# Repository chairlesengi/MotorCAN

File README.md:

# MotorCAN
CANBus based FOC motor driver board designed for drone gimbal motors for node-based control, designed in KiCad.

Features:
  - STM32G431 processor core for SimpleFOC software and CAN communication
  - 3.3V CAN communication for easy logic level support
  - Runs on 20-26V DC
  - Integrated magnetic absolute encoder (MT6816CT)
  - Handles up to ~3A of motor current

This driver is designed to be a fully integrated solution that mounts to the back of a gimbal motor with a diametrically magnetized magnet. For that reason, it includes an absoulute magnetic encoder and leverages the current sensing capabilities of the DRV8316C driver to maintain a continous measurement of the position of the rotor of the motor and its magnetic field. Then, the STM32 running SimpleFOC calculates the exact currents on each phase needed to create a magnetic torque on the motor that is 90 degrees from the magnetic field and therefore gives the greatest overall control of the motor. This chip also has a 3.3V CAN chip so it can link up to a simple 4 wire network of muliple of these boards for applications like camera gimbals.

Credits:
SimpleFOC: https://github.com/simplefoc
KiCad: https://www.kicad.org

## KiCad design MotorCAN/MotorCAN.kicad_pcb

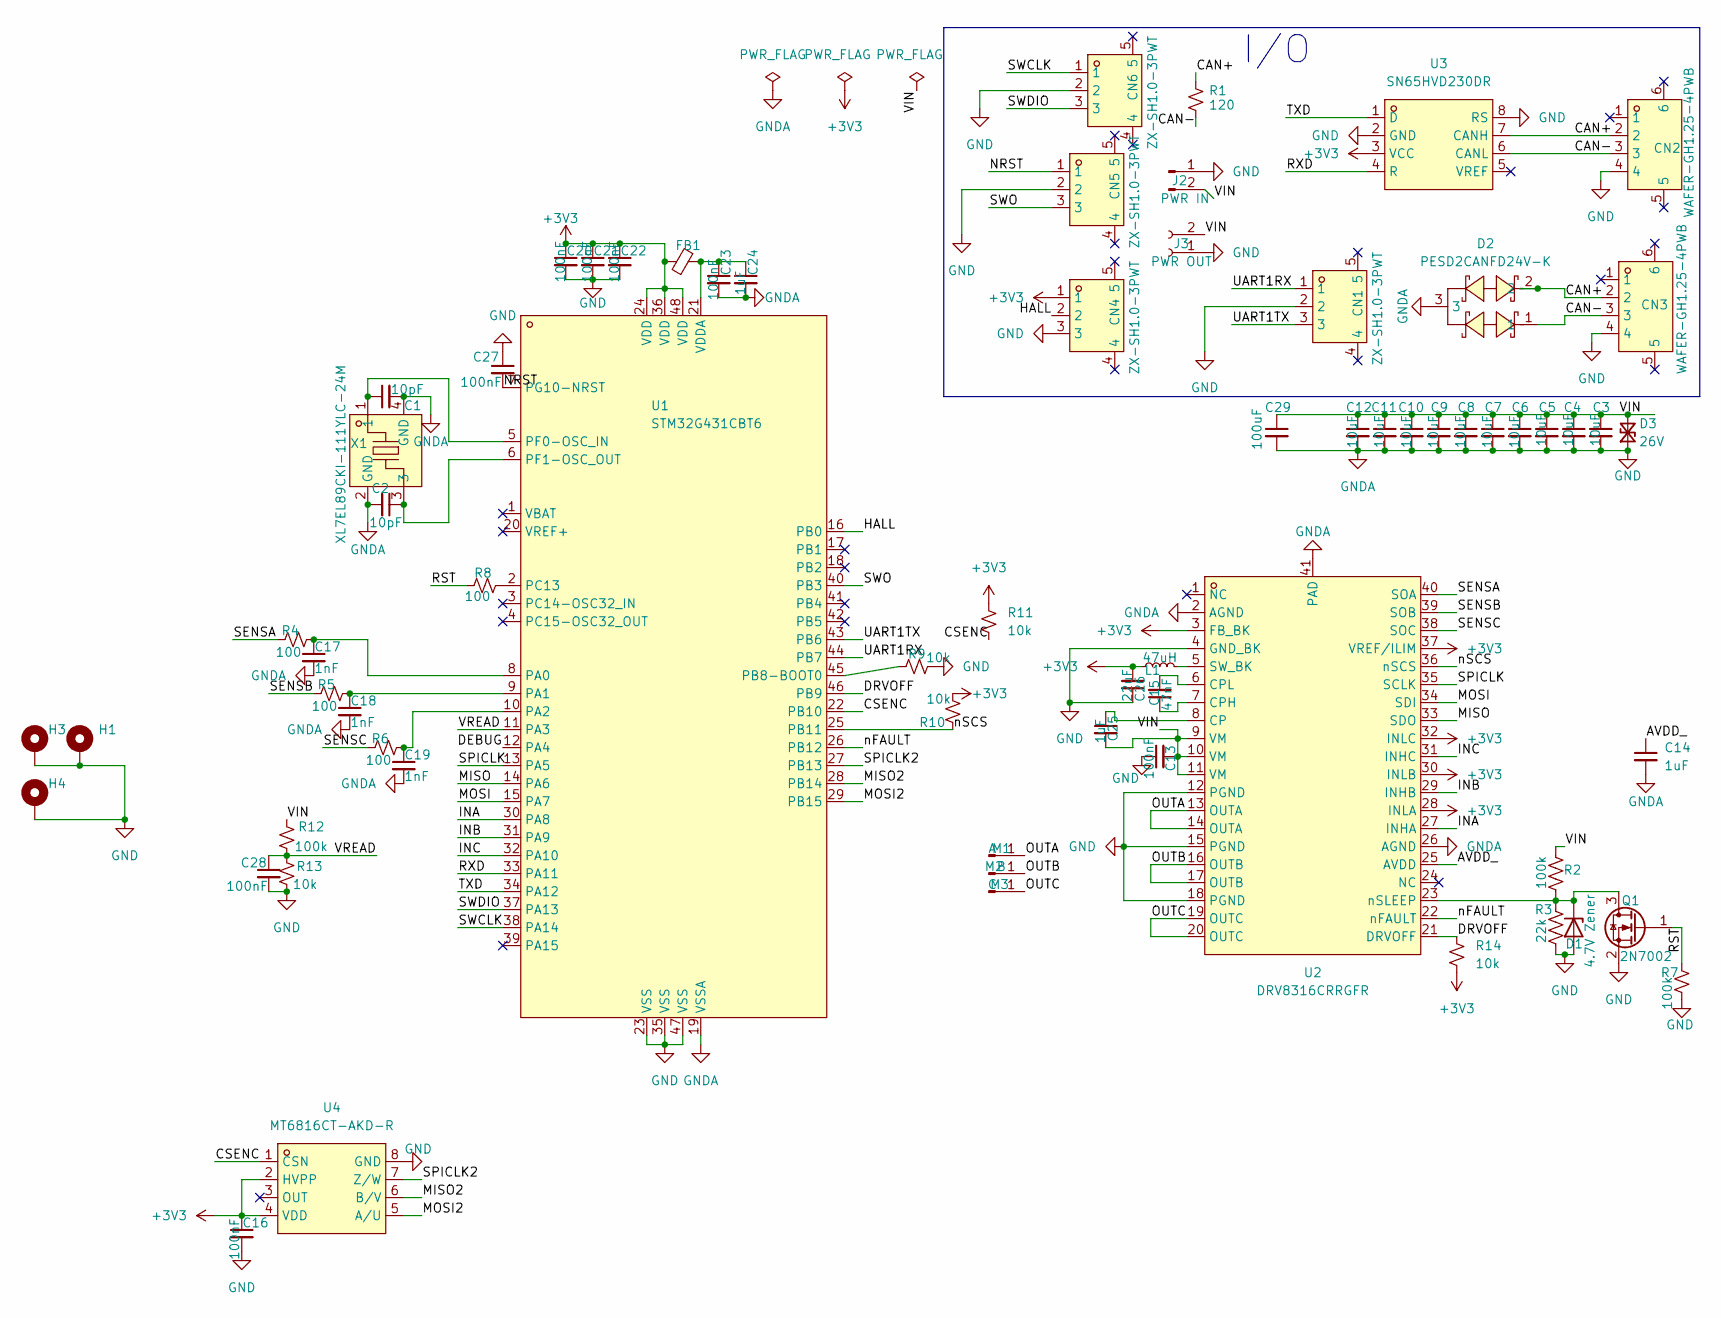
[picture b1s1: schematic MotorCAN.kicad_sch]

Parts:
C1, C2: 10pF; C_0402_1005Metric
C3, C4, C5, C6, C7, C8, C9, C10, C11, C12: 10uF; C_1206_3216Metric
C13, C16, C20, C21, C22, C23, C27, C28: 100nF; C_0402_1005Metric
C14, C24, C25: 1uF; C_0603_1608Metric
C15: 47nF; C_0603_1608Metric
C17, C18, C19: 1nF; C_0603_1608Metric
C26: 22uF; C_1206_3216Metric
C29: 100uF; CP_Elec_6.3x7.7
CN1, CN4, CN5, CN6: ZX-SH1.0-3PWT; CONN-SMD_3P-P1.00_MEGASTAR_ZX-SH1.0-3PWT; MPN ZX-SH1.0-3PWT; LCSC Part C7430445
CN2, CN3: WAFER-GH1.25-4PWB; CONN-SMD_4P-P1.25_XUNPU_WAFER-GH1.25-4PWB; MPN WAFER-GH1.25-4PWB; LCSC Part C3029379
D1: 4.7V Zener; D_SOD-123
D2: PESD2CANFD24V-K; SOT-23-3_L2.9-W1.3-P1.90-LS2.4-BR; MPN PESD2CANFD24V-K; LCSC Part C5278878
D3: 26V; D_SMB
FB1: 600@100MHz; R_0603_1608Metric
H1, H3, H4: MountingHole_Pad; MountingHole_2.2mm_M2_ISO14580_Pad_TopBottom
J2: PWR IN; AMASS_XT30PW-M_1x02_P2.50mm_Horizontal
J3: PWR OUT; AMASS_XT30PW-F_1x02_P2.50mm_Horizontal
L1: 47uH; IND-SMD_L4.0-W4.0
M1: A; SolderWirePad_1x01_SMD_2x4mm
M2: B; SolderWirePad_1x01_SMD_2x4mm
M3: C; SolderWirePad_1x01_SMD_2x4mm
Q1: 2N7002; SOT-23
R1: 120; R_0603_1608Metric
R2, R7, R12: 100k; R_0603_1608Metric
R3: 22k; R_0603_1608Metric
R4, R5, R6, R8: 100; R_0603_1608Metric
R9, R10, R11, R13, R14: 10k; R_0603_1608Metric
U1: STM32G431CBT6; LQFP-48_L7.0-W7.0-P0.50-LS9.0-BL; MPN STM32G431CBT6; LCSC Part C529355
U2: DRV8316CRRGFR; VQFN-40_L7.0-W5.0-P0.50-BL-EP5.7; MPN DRV8316CRRGFR; LCSC Part C5447274
U3: SN65HVD230DR; SOIC-8_L4.9-W3.9-P1.27-LS6.0-BL; MPN SN65HVD230DR; LCSC Part C12084
U4: MT6816CT-AKD-R; SOP-8_L4.9-W3.9-P1.27-LS6.0-BL-1; MPN MT6816CT-AKD-R; LCSC Part C2987620
X1: XL7EL89CKI-111YLC-24M; CRYSTAL-SMD_4P-L2.0-W1.6-BL-A; MPN XL7EL89CKI-111YLC-24M; LCSC Part C2965580

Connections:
+3V3: C16.1, C20.1, C21.1, C22.1, C26.2, CN4.1, FB1.1, L1.1, R10.1, R11.1, R14.2, U1.24 (VDD), U1.36 (VDD), U1.48 (VDD), U2.3 (FB_BK), U2.28 (INLA), U2.30 (INLB), U2.32 (INLC), U2.37 (VREF/ILIM), U3.3 (VCC), U4.2 (HVPP), U4.4 (VDD)
/AVDD_: C14.1, U2.25 (AVDD)
/CAN+: CN2.2, CN3.2, D2.2, R1.1, U3.7 (CANH)
/CAN-: CN2.3, CN3.3, D2.1, R1.2, U3.6 (CANL)
/CSENC: R11.2, U1.22 (PB10), U4.1 (CSN)
/DEBUG: U1.12 (PA4)
/DRVOFF: R14.1, U1.46 (PB9), U2.21 (DRVOFF)
/HALL: CN4.2, U1.16 (PB0)
/INA: U1.30 (PA8), U2.27 (INHA)
/INB: U1.31 (PA9), U2.29 (INHB)
/INC: U1.32 (PA10), U2.31 (INHC)
/MISO: U1.14 (PA6), U2.33 (SDO)
/MISO2: U1.28 (PB14), U4.6 (B/V)
/MOSI: U1.15 (PA7), U2.34 (SDI)
/MOSI2: U1.29 (PB15), U4.5 (A/U)
/NRST: C27.2, CN5.1, U1.7 (PG10-NRST)
/OUTA: M1.1 (Pin_1_1), U2.13 (OUTA), U2.14 (OUTA)
/OUTB: M2.1 (Pin_1_1), U2.16 (OUTB), U2.17 (OUTB)
/OUTC: M3.1 (Pin_1_1), U2.19 (OUTC), U2.20 (OUTC)
/RST: Q1.1 (G), R7.1, R8.1
/RXD: U1.33 (PA11), U3.4 (R)
/SENSA: R4.1, U2.40 (SOA)
/SENSB: R5.1, U2.39 (SOB)
/SENSC: R6.1, U2.38 (SOC)
/SPICLK: U1.13 (PA5), U2.35 (SCLK)
/SPICLK2: U1.27 (PB13), U4.7 (Z/W)
/SWCLK: CN6.1, U1.38 (PA14)
/SWDIO: CN6.3, U1.37 (PA13)
/SWO: CN5.3, U1.40 (PB3)
/TXD: U1.34 (PA12), U3.1 (D)
/UART1RX: CN1.1, U1.44 (PB7)
/UART1TX: CN1.3, U1.43 (PB6)
/VIN: C3.1, C4.1, C5.1, C6.1, C7.1, C8.1, C9.1, C10.1, C11.1, C12.1, C13.2, C25.2, C29.1, D3.2 (A2), J2.2, J3.2, R2.1, R12.1, U2.9 (VM), U2.10 (VM), U2.11 (VM)
/VREAD: C28.1, R12.2, R13.1, U1.11 (PA3)
/nFAULT: U1.26 (PB12), U2.22 (nFAULT)
/nSCS: R10.2, U1.25 (PB11), U2.36 (nSCS)
GND: C1.2, C2.2, C3.2, C4.2, C5.2, C6.2, C7.2, C8.2, C9.2, C10.2, C11.2, C12.2, C13.1, C14.2, C16.2, C17.2, C18.2, C19.2, C20.2, C21.2, C22.2, C23.2, C24.2, C26.1, C27.1, C28.2, C29.2, CN1.2, CN2.4, CN3.4, CN4.3, CN5.2, CN6.2, D1.2 (A), D2.3, D3.1 (A1), H1.1 (1_1), H3.1 (1_1), H4.1 (1_1), J2.1, J3.1, Q1.2 (S), R3.2, R7.2, R9.2, R13.2, U1.19 (VSSA), U1.23 (VSS), U1.35 (VSS), U1.47 (VSS), U2.2 (AGND), U2.4 (GND_BK), U2.12 (PGND), U2.15 (PGND), U2.18 (PGND), U2.26 (AGND), U2.41 (PAD), U3.2 (GND), U3.8 (RS), U4.8 (GND), X1.2 (GND), X1.4 (GND)
unnamed: D1.1 (K), Q1.3 (D), R2.2, R3.1, U2.23 (nSLEEP)
unnamed: C17.1, R4.2, U1.8 (PA0)
unnamed: C18.1, R5.2, U1.9 (PA1)
unnamed: C19.1, R6.2, U1.10 (PA2)
unnamed: R9.1, U1.45 (PB8-BOOT0)
unnamed: R8.2, U1.2 (PC13)
unnamed: C1.1, U1.5 (PF0-OSC_IN), X1.1
unnamed: C2.1, U1.6 (PF1-OSC_OUT), X1.3
unnamed: C23.1, C24.1, FB1.2, U1.21 (VDDA)
unnamed: C25.1, U2.8 (CP)
unnamed: C15.1, U2.7 (CPH)
unnamed: C15.2, U2.6 (CPL)
unnamed: L1.2, U2.5 (SW_BK)

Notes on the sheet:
I/O

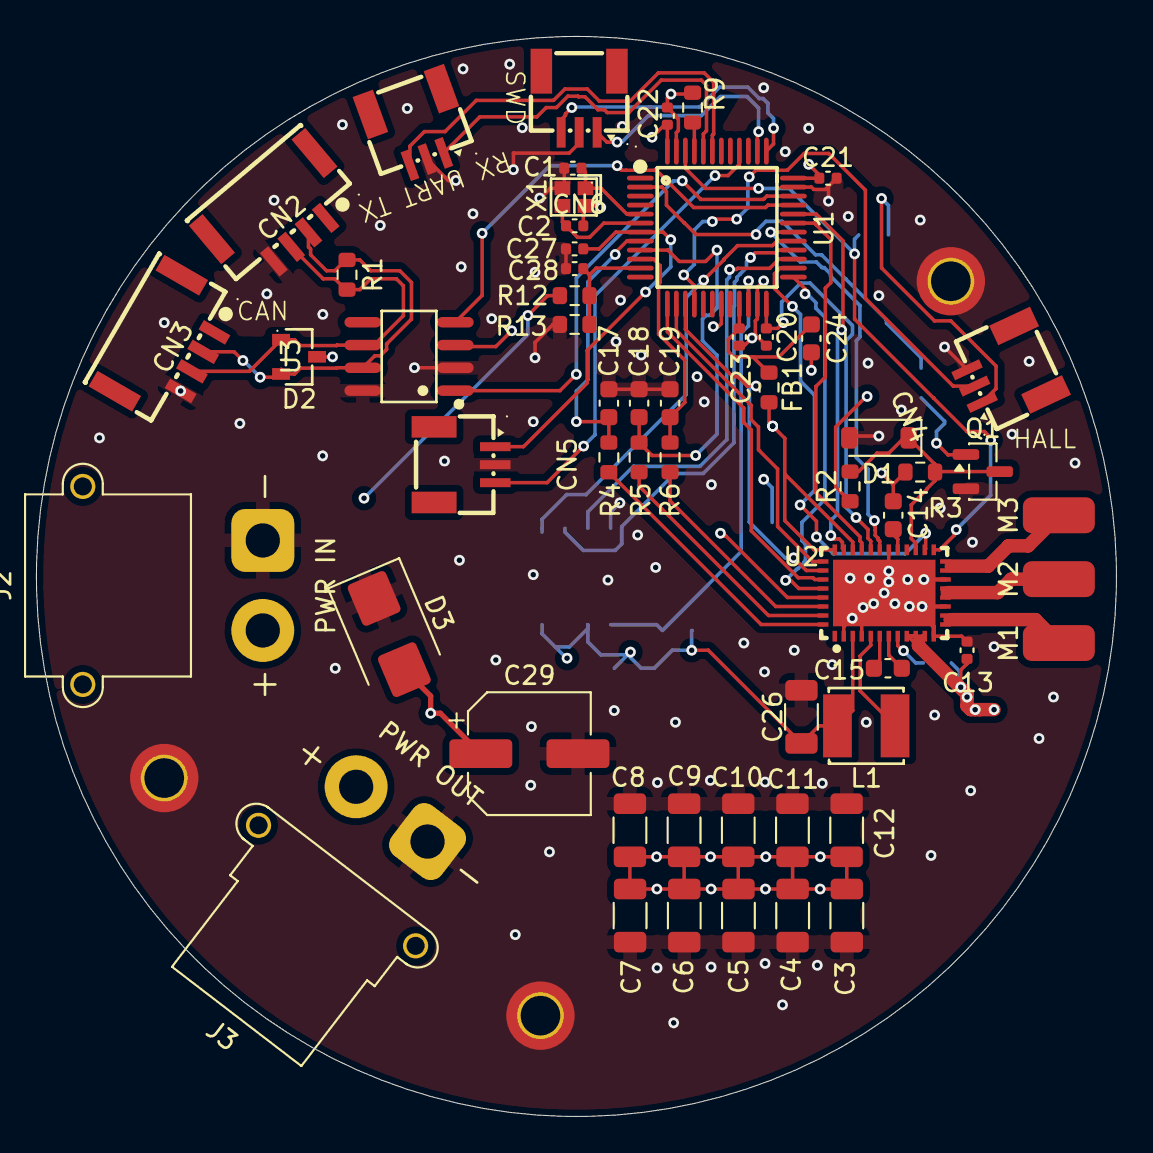
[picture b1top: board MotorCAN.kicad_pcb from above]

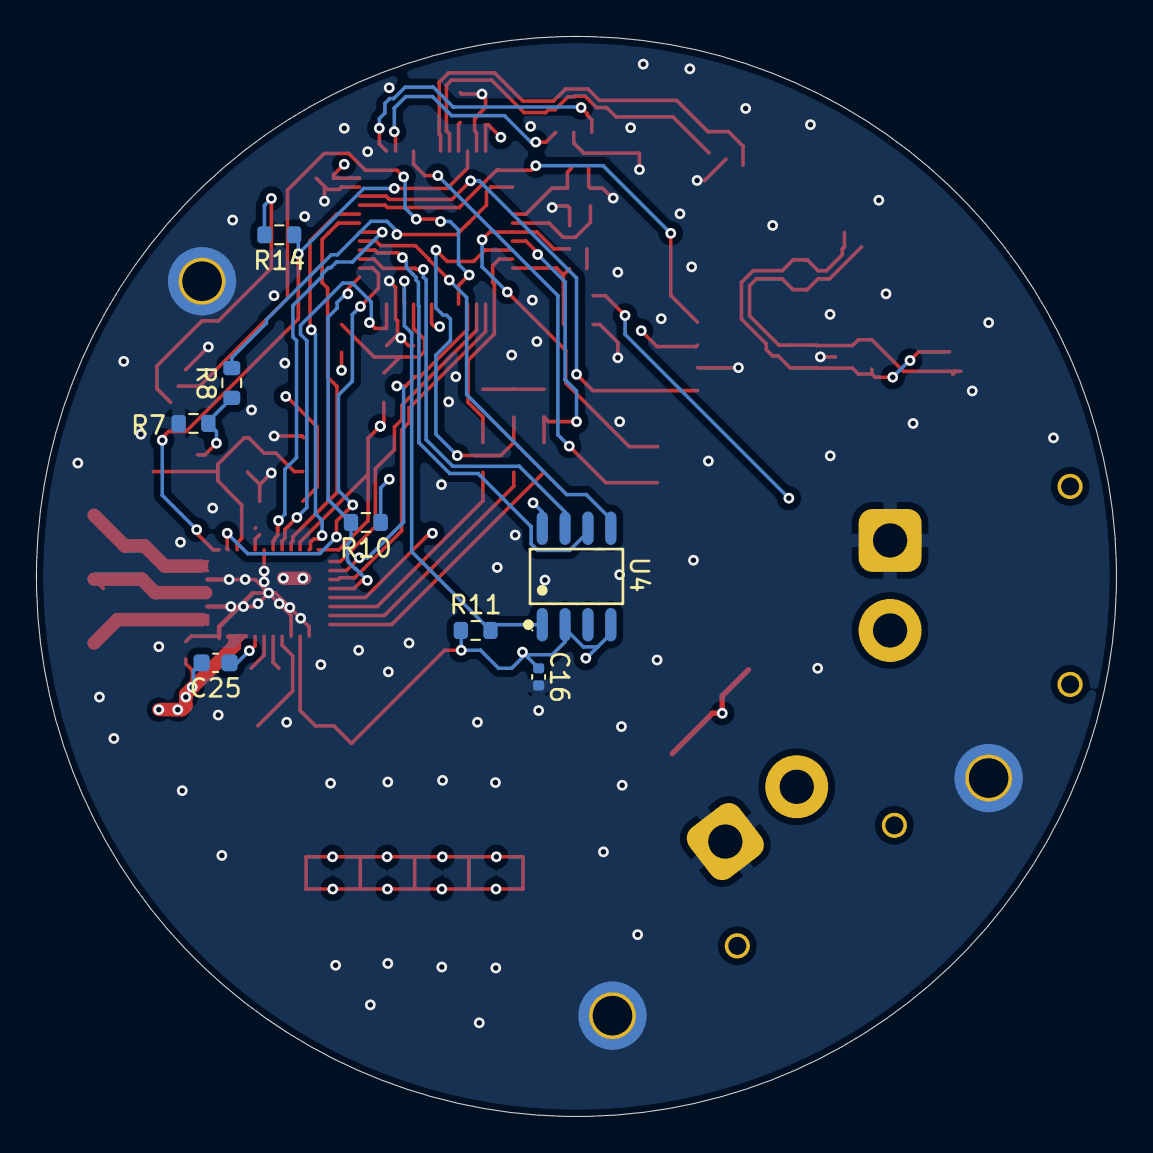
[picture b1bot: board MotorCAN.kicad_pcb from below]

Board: 4 copper layers, 60.0 x 60.0 mm, 68 parts (8 on the bottom side), 49 nets.

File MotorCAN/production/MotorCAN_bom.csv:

Designator,Footprint,Quantity,Value,LCSC Part #
"C1, C2",0402,2,10pF,
"C10, C11, C12, C3, C4, C5, C6, C7, C8, C9",1206,10,10uF,
"C13, C16, C20, C21, C22, C23, C27, C28",0402,8,100nF,
"C14, C24, C25",0603,3,1uF,
C15,0603,1,47nF,
"C17, C18, C19",0603,3,1nF,
C26,1206,1,22uF,
C29,CP_Elec_6.3x7.7,1,100uF,
"CN1, CN4, CN5, CN6",CONN-SMD_3P-P1.00_MEGASTAR_ZX-SH1.0-3PWT,4,ZX-SH1.0-3PWT,C7430445
"CN2, CN3",CONN-SMD_4P-P1.25_XUNPU_WAFER-GH1.25-4PWB,2,WAFER-GH1.25-4PWB,C3029379
D1,D_SOD-123,1,4.7V Zener,
D2,SOT-23-3_L2.9-W1.3-P1.90-LS2.4-BR,1,PESD2CANFD24V-K,C5278878
D3,D_SMB,1,26V,
FB1,0603,1,600@100MHz,
J2,AMASS_XT30PW-M_1x02_P2.50mm_Horizontal,1,PWR IN,
J3,AMASS_XT30PW-F_1x02_P2.50mm_Horizontal,1,PWR OUT,
L1,IND-SMD_L4.0-W4.0,1,47uH,C18222004
M1,SolderWirePad_1x01_SMD_2x4mm,1,A,
M2,SolderWirePad_1x01_SMD_2x4mm,1,B,
M3,SolderWirePad_1x01_SMD_2x4mm,1,C,
Q1,SOT-23,1,2N7002,
R1,0603,1,120,
"R10, R11, R13, R14, R9",0603,5,10k,
"R12, R2, R7",0603,3,100k,
R3,0603,1,22k,
"R4, R5, R6, R8",0603,4,100,
U1,LQFP-48_L7.0-W7.0-P0.50-LS9.0-BL,1,STM32G431CBT6,C529355
U2,VQFN-40_L7.0-W5.0-P0.50-BL-EP5.7,1,DRV8316CRRGFR,C5447274
U3,SOIC-8_L4.9-W3.9-P1.27-LS6.0-BL,1,SN65HVD230DR,C12084
U4,SOP-8_L4.9-W3.9-P1.27-LS6.0-BL-1,1,MT6816CT-AKD-R,C2987620
X1,CRYSTAL-SMD_4P-L2.0-W1.6-BL-A,1,XL7EL89CKI-111YLC-24M,C2965580

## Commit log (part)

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2026-06-06 Create README.md
    Expanded project description and added features list.
2026-06-06 Added .pcb, .sch from previous work
    Had worked on project before putting on github so moving files in done now
2026-06-06 ok actually now I fixed the repo
    Yayy
2026-06-06 Fix again maybe
